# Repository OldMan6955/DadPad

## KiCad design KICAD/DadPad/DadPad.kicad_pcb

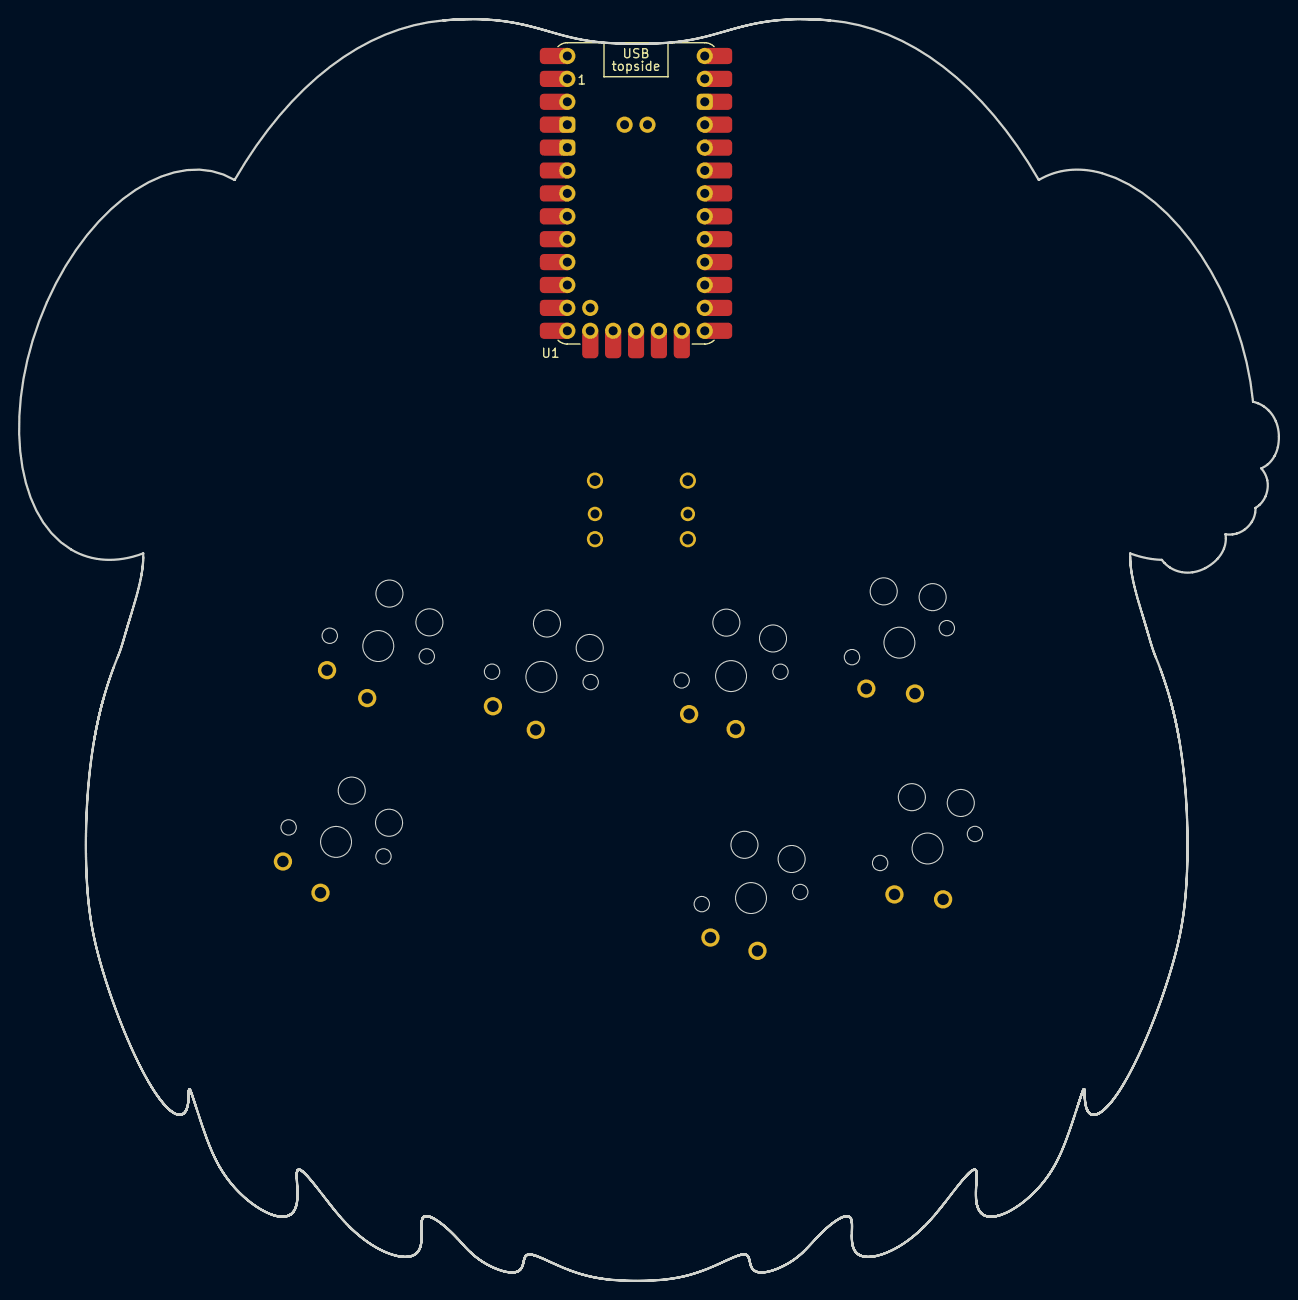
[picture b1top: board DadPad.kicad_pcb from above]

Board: 2 copper layers, 139.7 x 139.9 mm, 9 parts (0 on the bottom side), 13 nets, no tracks yet.

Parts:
HAT1: 5Way-Tactile_K1-1506DN-01; 5Way-non-reverse no silk 3D Model
SW1, SW3, SW4, SW5, SW6, SW7: SW_Push; Kailh_ChocV1_HS_Sol_SOCKETxPURPZx1uMBK_white
SW2: SW_Push; Kailh_ChocV1_HS_Sol_SOCKETxPURPZx1uMBK_GOLD
U1: Pluto; Helios_ACH Helios 3D

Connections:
001: SW1.1, U1.15 (RST)
002: SW2.1, U1.16 (3V3)
003: SW3.1, U1.17 (P29)
004: SW4.1, U1.18 (P28)
005: SW5.1, U1.19 (P27)
5WAY 001: HAT1.1, U1.5 (P2)
5WAY 002: HAT1.2, U1.6 (P3)
5WAY 003: HAT1.3, U1.7 (P4)
5WAY 004: HAT1.5, U1.8 (P5)
5WAY 005: HAT1.6, U1.9 (P6)
006: SW6.1, U1.20 (P26)
007: SW7.1, U1.21 (P22)
GND: HAT1.4, SW1.2, SW2.2, SW3.2, SW4.2, SW5.2, SW6.2, SW7.2, U1.3 (GND), U1.4 (GND), U1.14 (GND)

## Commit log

2023-11-10 first push
